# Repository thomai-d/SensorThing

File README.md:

# SensorThing
ESP8266 + DHT22 RoomSensor

## Features
- Runs with 4x AA batteries (21µA Standby current => 1+ years runtime)
- Measures temperature, relative humidity and battery voltage
- Calculates dew point and absolute humidity
- Pushes data via HTTP POST to server

## Schematics

EAGLE files, see repository.

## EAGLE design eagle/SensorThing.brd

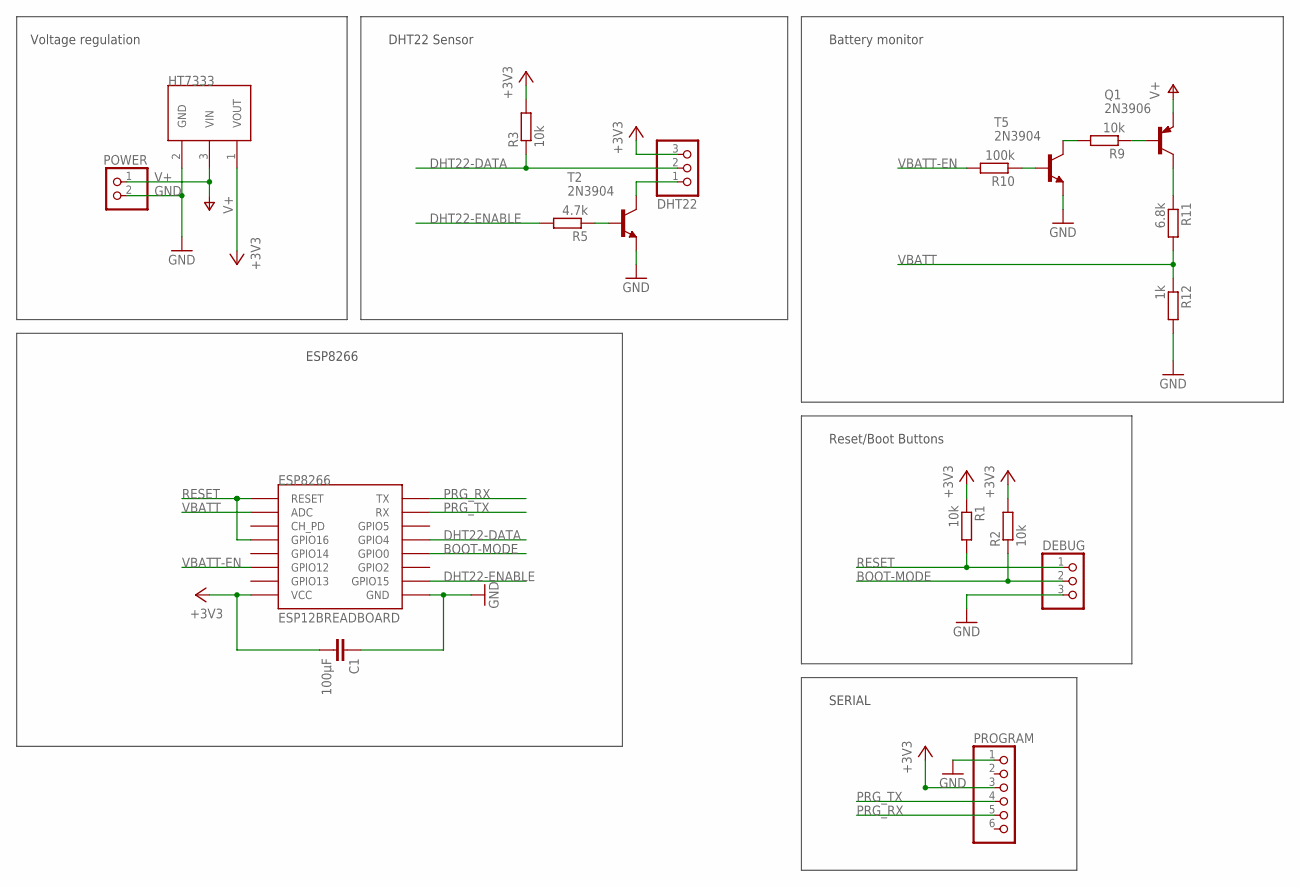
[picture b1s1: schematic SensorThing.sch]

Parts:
C1: 100µF; C025-024X044
DEBUG: 1X03/90
DHT22: 1X03/90
ESP8266: ESP12BREADBOARD; ESP12E-BREADBOARD
HT7333: HT73XX; SOT89-R
POWER: 1X02/90
PROGRAM: 1X06/90
Q1: 2N3906; TO92
R1, R2, R3, R9: 10k; 0204/7
R5: 4.7k; M0805
R10: 100k; M0805
R11: 6.8k; 0204/7
R12: 1k; M0805
T2, T5: 2N3904; TO92

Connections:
+3V3: C1.2, DHT22.3, ESP8266.8 (VCC), HT7333.1 (VOUT), PROGRAM.3, R1.1, R2.2, R3.2
BOOT-MODE: DEBUG.2, ESP8266.12 (GPIO0), R2.1
DHT22-DATA: DHT22.2, ESP8266.13 (GPIO4), R3.1
DHT22-ENABLE: ESP8266.10 (GPIO15), R5.2
GND: C1.1, DEBUG.3, ESP8266.9 (GND), HT7333.2 (GND), POWER.2, PROGRAM.1, R12.2, T2.3 (E), T5.3 (E)
unnamed: R5.1, T2.2 (B)
unnamed: DHT22.1, T2.1 (C)
unnamed: R9.2, T5.1 (C)
unnamed: R10.1, T5.2 (B)
unnamed: Q1.1 (C), R11.1
unnamed: Q1.2 (B), R9.1
PRG_RX: ESP8266.16 (TX), PROGRAM.5
PRG_TX: ESP8266.15 (RX), PROGRAM.4
RESET: DEBUG.1, ESP8266.1 (RESET), ESP8266.4 (GPIO16), R1.2
V+: HT7333.3 (VIN), POWER.1, Q1.3 (E)
VBATT: ESP8266.2 (ADC), R11.2, R12.1
VBATT-EN: ESP8266.6 (GPIO12), R10.2

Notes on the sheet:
Voltage regulation
DHT22 Sensor
Battery monitor
Reset/Boot Buttons
SERIAL
ESP8266

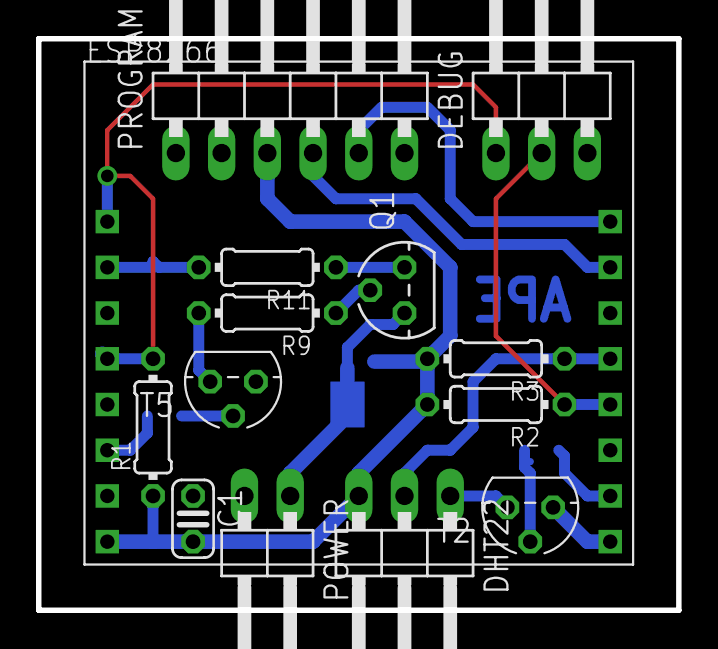
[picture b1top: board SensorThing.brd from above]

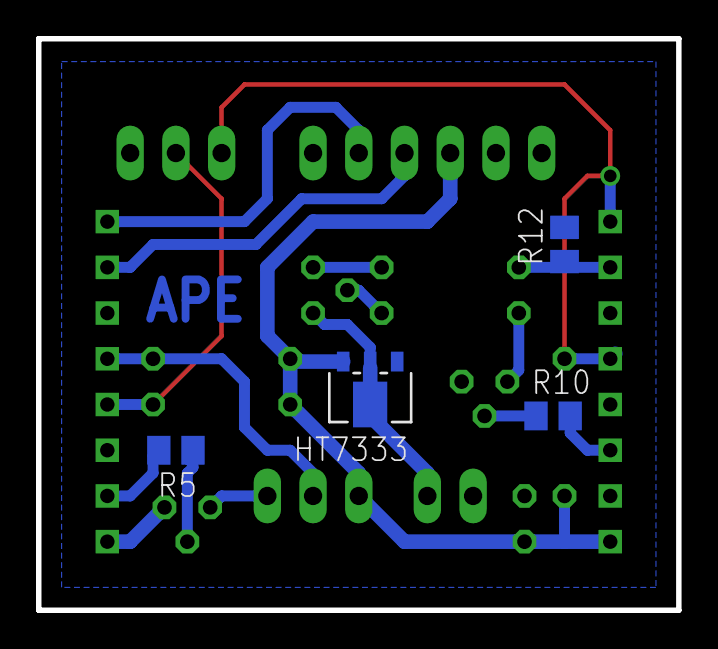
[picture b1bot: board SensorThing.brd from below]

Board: 2 copper layers, 35.6 x 31.8 mm, 18 parts (4 on the bottom side), 17 nets.

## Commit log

2017-11-02 Added source code
2017-11-02 Added readme & images
2017-11-02 Added eagle files
